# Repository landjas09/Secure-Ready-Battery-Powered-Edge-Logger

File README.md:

# Secure-Ready Battery-Powered Edge Logger

A custom ESP32-C3 hardware/firmware platform, developed across two revisions — from a general-purpose IoT sensor board into a battery-aware, timestamped, secure-ready edge data logger. Designed end-to-end in KiCad, ported to Zephyr RTOS.
This repository contains the full hardware design (schematics, PCB layout, BOM) for both revisions.

---

## Overview

The project began as the **IoT Development Board** (**Rev 1**) — a general-purpose ESP32-C3 sensor/data-logging platform: WiFi/BLE connectivity, environmental and ambient-light sensing, audio capture, local storage, and LiPo charging on a single compact PCB.

**Rev 2, the Secure-Ready Battery-Powered Edge Logger**, evolved that platform with a regulated buck-boost power stage holding 3.3V across the full LiPo discharge range, a battery fuel gauge with Kelvin current sensing, a battery-backed real-time clock for offline timestamping, and a hardware secure element for protected device identity and cryptographic key storage. The name change is deliberate, not cosmetic — it reflects the shift from a general-purpose development board to a system built around a specific mission: unattended, battery-aware, timestamped, secure-ready edge logging.

Both revisions share the same core sensing/storage/connectivity architecture; Rev 2 adds the hardware needed to take the board from *prototype* toward *deployable product*.

---

## Repository Structure

```
├── hardware/
│   ├── rev1/                     # IoT Development Board (original revision)
│   │   ├── README.md             # Full hardware documentation for Rev 1
│   │   └── ...                   # KiCad project, BOM, libraries
│   │
│   └── rev2/                     # Secure-Ready Battery-Powered Edge Logger (current revision)
│       ├── README.md             # Full hardware documentation for Rev 2
│       └── ...                   # KiCad project, BOM, libraries
│

│
└── README.md                     # This file
```

> Each revision is self-contained — its own KiCad project, its own Gerbers/BOM, and its own README with full component-level documentation, block diagrams, and design notes. Start here for the high-level picture, then go to the revision folder for detail.

---

## Hardware Revisions at a Glance

| | Rev 1 — IoT Development Board | Rev 2 — Secure Edge Logger |
|---|---|---|
| MCU | ESP32-C3-WROOM-02-H4 | ESP32-C3-WROOM-02-H4 |
| Power regulation | LM1117-3.3 linear regulator | TPS63802 buck-boost (regulated 3.3V across full LiPo range) |
| Battery charging | MCP73871 (charge + power-path) | MCP73871 (unchanged) |
| Battery state monitoring | Charge-status LEDs only | + BQ27441-G1A fuel gauge, 10mΩ Kelvin current sensing |
| Timekeeping | None (network time only) | + DS3231SN battery-backed RTC |
| Security | None | + NXP EdgeLock SE050E2 secure element |
| Storage | microSD + W25Q32 SPI NOR flash | microSD + W25Q32 SPI NOR flash (unchanged) |
| Sensing | BME280, TEMT6000X01, mic + MAX4466 preamp | Unchanged |
| Connectivity | USB-C, CP2102N USB-UART, OLED I²C header | Unchanged |
| Firmware target | Zephyr RTOS | Zephyr RTOS |

Full rationale for each Rev 2 change — including the buck-boost layout, Kelvin sensing wiring, and shared I²C bus considerations across five devices — is documented in [`hardware/rev2_secure-edge-logger/README.md`](hardware/rev2_secure-edge-logger/README.md).

---

## Design Evolution: The Engineering Behind Rev 1 → Rev 2

Rev 1 answered a narrower question: *can this sensing/connectivity architecture work on a single ESP32-C3 board?* It did — but running it as something closer to an actual field-deployed logger, rather than a bench prototype, surfaced four real limitations that Rev 1's architecture had no answer for. Rev 2 exists specifically to close those four gaps.

**1. The power rail wasn't guaranteed across the battery's actual operating range.**
The LM1117 is a linear regulator — it can only step *down*, and needs a few hundred millivolts of headroom above 3.3V to stay in regulation. A single-cell LiPo spends a meaningful portion of its discharge curve at or below that threshold, well before the cell is actually empty. In practice, that meant the system rail could sag or brown out with real battery capacity still remaining — the board would report "low battery" behavior driven by the regulator's limits, not the battery's. The **TPS63802 buck-boost** converter can step the rail up *or* down as needed, holding a stable 3.3V across the LiPo's full discharge range. The trade-off is real: an inductor-based switching regulator is a more complex layout than a 3-pin LDO (switching-node placement, input/output capacitor proximity), but it removes an artificial ceiling on usable battery capacity.

**2. Battery state was inferred, not measured.**
Rev 1's only battery-state signal was the MCP73871's charge-status LEDs — charging, charged, or power-good. That tells you the *charger's* state, not the battery's: no state-of-charge percentage, no remaining runtime estimate, no visibility into battery health over repeated cycles. For a device meant to log unattended in the field, "the LED is off" isn't useful data. The **BQ27441-G1A fuel gauge**, paired with a 10mΩ Kelvin-sensed shunt for accurate current measurement, gives the firmware real coulomb-counted state-of-charge and capacity data — the difference between guessing how much runtime is left and actually knowing.

**3. Timestamps depended on the network being present, and couldn't survive a real power interruption.**
The ESP32-C3 does have an internal RTC timer, and it runs independently of WiFi — but it has two limitations that make it unsuitable as the sole time source for an offline logger. First, it has no absolute time reference of its own; it only counts elapsed ticks, so it needs to be told the actual date/time at least once, which in Rev 1 meant NTP over WiFi. Second, and more importantly, it has no dedicated backup power domain — it's powered from the same rail as the rest of the chip, so a genuine power interruption (battery disconnected, fully depleted) resets it, and any subsequent logging either loses accurate timestamping or needs a full resync before it can be trusted again. That's a direct conflict with the point of an edge logger, which by definition needs to keep working — and keep accurate time — when disconnected or power-cycled. The **DS3231SN**, with its own dedicated backup supply, keeps ticking through main-power interruptions entirely independently of the ESP32-C3 and of network availability — log integrity no longer depends on the device staying connected or staying powered.

**4. There was no way to prove a device's identity, or protect anything it might need to keep secret.**
Rev 1 had no mechanism for device authentication at all. Any private key or credential would have had to live in the ESP32-C3's own flash — readable by anyone who can extract the chip's contents, meaning a physically compromised device could be cloned or impersonated with no way to detect it. The **SE050E2 secure element** generates and stores keys internally and performs signing/crypto operations without ever exposing key material to the application processor. This is explicitly a *hardware readiness* change, not a finished feature — the chip makes protected device identity possible; actual authentication behavior still has to be implemented and provisioned at the firmware level.

Taken together, Rev 1 — the **IoT Development Board** — validated *that the concept works*. Rev 2 — the **Secure-Ready Battery-Powered Edge Logger** — is the set of changes needed to start asking whether it could actually be *trusted and deployed*: accurate power delivery, real battery visibility, time integrity without a network, and a hardware root of trust. The rename reflects that shift, from a general platform to a system built for a specific job.

---

## Firmware

Both revisions target a common **Zephyr RTOS** board port (`iot_sensor_node_esp32c3`), built from scratch rather than as an overlay on an existing Espressif reference board — the SoC layer is inherited from Zephyr's existing ESP32-C3 support, with Devicetree, pinctrl, and Kconfig scoped to this board's actual hardware.

See [`zephyr/README.md`](https://github.com/landjas09/Zephyr-RTOS-Port/blob/db37eb44f9d1a81693981f7a8ff599a05c521f56/README.md) for the full board architecture, peripheral integration (I²C, SPI, ADC, UART, GPIO), debugging/OpenOCD setup, and the specific integration issues encountered and resolved during the port.

---

## Design Tools

- **Schematic capture & PCB layout:** KiCad 10
- **Electrical/design verification:** KiCad ERC & DRC
- **Firmware / board support:** Zephyr RTOS
- **Secure-element middleware:** NXP Plug & Trust (SE050E2)
- **Hardware configuration:** Silicon Labs Simplicity Studio / Xpress Configurator

---

## Where to Go Next

- **New to the project?** Start with [`hardware/rev1_iot-development-board/README.md`](hardware/rev1_iot-development-board/README.md) for the original, simpler architecture.
- **Interested in the current hardware?** Go to [`hardware/rev2_secure-edge-logger/README.md`](hardware/rev2_secure-edge-logger/README.md) for the full secure edge-logger design.
- **Interested in the firmware/RTOS side?** Go to [`zephyr/README.md`](https://github.com/landjas09/Zephyr-RTOS-Port/blob/db37eb44f9d1a81693981f7a8ff599a05c521f56/README.md) for the board port documentation.

---

## Acknowledgments

Board design informed by manufacturer reference designs and application notes from Espressif, Microchip, Texas Instruments, NXP, Analog Devices/Maxim, Silicon Labs, Bosch Sensortec, Winbond, and the Zephyr Project.

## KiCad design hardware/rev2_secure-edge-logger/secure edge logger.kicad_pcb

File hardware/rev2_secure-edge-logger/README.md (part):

# Secure-Ready Battery-Powered Edge Logger

**ESP32-C3 · KiCad 10 · Zephyr RTOS · Battery monitoring · Offline timekeeping · Secure element**

A custom embedded platform for collecting environmental, light, and acoustic signals, storing data locally, and developing battery-aware logging applications. The hardware combines an ESP32-C3 with a buck-boost power supply, a fuel gauge, a battery-backed RTC, and a dedicated secure element.

*CAD rendering of the revised design. Hardware fabrication and bench validation are pending.*

| Project area | Current state |
|---|---|
| Hardware | Rev 2 schematic and PCB design in KiCad 10 |
| Firmware | Custom Zephyr board port; build validation reported in the firmware repository |
| Physical validation | Pending PCB fabrication and bring-up |
| Security | SE050E2 hardware and middleware integration; application provisioning remains to be completed |
| Manufacturing | NextPCB is the intended manufacturer; procurement and release checks remain open |

## Contents

- [Design evolution](#design-evolution)
- [Rev 2 hardware](#rev-2-hardware)
- [Power architecture](#power-architecture)
- [Interfaces and pin mapping](#interfaces-and-pin-mapping)
- [Programming and debugging](#programming-and-debugging)
- [Firmware integration](#firmware-integration)
- [Manufacturing and validation](#manufacturing-and-validation)
- [Repository and design files](#repository-and-design-files)
- [Technical references](#technical-references)

## Design evolution

The project began as the **IoT Development Board**, a general-purpose ESP32-C3 design combining sensing, wireless connectivity, local storage, USB-to-UART programming, and single-cell battery charging.

**Rev 2** develops that architecture around unattended data logging. Its main additions address supply regulation as the battery discharges, visibility into battery state, timekeeping without a network connection, and protected cryptographic credentials.

| Function | Rev 1 — IoT Development Board | Rev 2 — Secure Edge Logger |
|---|---|---|
| Controller | ESP32-C3-WROOM-02-H4 | ESP32-C3-WROOM-02-H4 |
| System regulation | LM1117-3.3 linear regulator | TPS63802 buck-boost converter |
| Charging / load sharing | MCP73871 | MCP73871 |
| Battery monitoring | Charger status outputs | BQ27441-G1A and 10 mΩ four-terminal shunt |
| Absolute time | Requires a software time source | DS3231SN with separate backup-cell connection |
| Security hardware | ESP32-C3 platform capabilities | Adds NXP EdgeLock SE050E2 |
| Sensors | BME280, TEMT6000, electret microphone and MAX4466 | Same sensing architecture |
| Local storage | External SPI NOR and SD-card socket | Same architecture, with revised bus pull-ups |
| Programming interface | USB-to-UART architecture | CP2102N-A02-GQFN24 with dedicated DTR/RTS outputs |

A linear regulator requires input headroom above its output. A 1S LiPo supply eventually falls below the voltage needed to maintain a regulated 3.3 V rail through an LM1117. The buck-boost stage can both raise and lower its input voltage, extending the usable operating range. Final operation still depends on the pack cutoff, load, conversion losses, and thermal performance.

## Rev 2 hardware

| Subsystem | Reference | Selected device | Interface / role |
|---|---|---|---|
| MCU and radio | U203 | ESP32-C3-WROOM-02-H4 | RISC-V processor, 2.4 GHz Wi-Fi, Bluetooth LE, 4 MiB module flash |
| USB-to-UART | U200 | CP2102N-A02-GQFN24 | UART0 console and programming; DTR/RTS boot control |
| USB data protection | U201 | USBLC6-2SC6 | ESD protection on USB D+/D− |
| Charger / power path | U100 | MCP73871-2CAI/ML | 4.2 V single-cell charging and system load sharing |
| System regulator | IC100 | TPS63802DLAR | Nominal 3.3 V buck-boost conversion |
| Battery fuel gauge | IC101 | BQ27441DRZT-G1A | I²C battery-state estimation |
| Current sensing | R105 | WSK2512R0100FEA | 10 mΩ, four-terminal Kelvin shunt |
| Environmental sensing | U300 | BME280 | Temperature, humidity, and pressure over I²C |
| Ambient light | Q300 | TEMT6000X01 | Analog input to ADC1 |
| Acoustic input | MK300 / U303 | CMC-5042PF-AC / MAX4466EXK+T | Electret microphone and analog preamplifier |
| Real-time clock | U301 | DS3231SN# | I²C calendar/time, alarm or square-wave output |
| Secure element | U302 | SE050E2HQ1/Z01Z3Z | I²C transport for protected keys and cryptographic operations |
| External NOR | U202 | W25Q32JVSSIQ | 32 Mbit / 4 MiB SPI storage, separate from module flash |
| Removable storage | J200 | GSD090012SEU | **Full-size SD** socket, connected for SPI operation |

The microphone path exposes an analog waveform to the MCU. Sampling rate, filtering, calibration, and any acoustic metrics are application responsibilities. The light input likewise requires calibration before reporting an absolute illuminance value.

### PCB construction

The current CAD specifies a **four-layer, 1.60 mm PCB** with an approximate **82.0 × 54.2 mm** outline envelope. The outline includes an antenna clearance cutout; the CAD outline and connector drawings define the enclosure fit.

| Copper layer | Contents in the current design |
|---|---|
| F.Cu | Components, signal routing, and local power/ground pours |
| In1.Cu | Ground zone |
| In2.Cu | Power distribution zones |
| B.Cu | Additional signal routing |

The fabrication stackup and USB differential geometry must be agreed with NextPCB. The stackup stored in CAD alone does not establish the manufactured impedance.

## Power architecture

```mermaid
flowchart TD
    USB["USB-C: 5 V input"] --> FUSE["F100: resettable fuse"]
    FUSE --> MCP["MCP73871: charger and power path"]
    PACK["Protected 1S LiPo pack"] <--> SHUNT["R105: 10 mΩ current shunt"]
    SHUNT <--> MCP
    SHUNT -. "Kelvin sense" .-> GAUGE["BQ27441-G1A"]
    MCP --> SYS["MCP-OUT system supply"]
    SYS --> BUCK["TPS63802 buck-boost"]
    BUCK --> RAIL["3.3 V system rail"]
```

### Charging and system supply

- **Input:** 5 V USB power through J100. Separate 5.1 kΩ resistors terminate CC1 and CC2. The design has no USB Power Delivery controller.
- **Charge target:** the selected MCP73871 variant charges a 1S Li-ion/LiPo pack to 4.2 V. R114 = 2 kΩ requests approximately **500 mA** nominal charge current, subject to available input current and thermal regulation.
- **Input limit:** the current wiring selects the MCP73871 USB mode with a nominal **500 mA total input limit** (`SEL` low, `PROG2` high). The system and charger share that budget. A higher-rated USB adapter does not change these hardware settings.
- **Temperature sensing:** J102 connects an external battery thermistor. The sensor and harness must be selected for the charger and thermally coupled to the pack.
- **Pack protection:** use a qualified protected battery pack with suitable discharge, charge, and temperature ratings. Pack protection provides the required cell cutoff behavior; the charger manages charging and load sharing.

### 3.3 V regulation and battery measurement

The TPS63802 uses a 470 nH inductor and a 511 kΩ / 91 kΩ feedback divider for approximately 3.3 V. `EN` follows the system supply and `MODE` is tied low for power-save operation. The converter's rated current is a component specification; the board's continuous and peak current capability must be established for the complete power path.

The BQ27441 measures battery current across R105 using separate sense connections. Firmware must configure the gauge for the actual pack capacity, charge-termination behavior, and operating limits. Battery runtime, idle consumption, load-step margin, and charging temperature rise remain measurements to establish on the assembled board.

### RTC backup supply

BT300 is a **Keystone 2998 / 2998TR holder**, supplied separately from its cell. Its footprint accepts a 6.8 mm cell; it is incompatible with a CR2032.

The previously considered MS621FE is a rechargeable 3 V cell, but the current PCB provides **no RTC-cell charging circuit**. A final cell and charging/replacement plan must be qualified. Keep the backup supply within the DS3231's specified range, including its 2.3 V minimum. This backup connection supplies the RTC during loss of main power; it does not run the MCU or preserve an unfinished storage write.

## Interfaces and pin mapping

The following assignments come from the revised Rev 2 PCB connections.

### MCU signals

| ESP32-C3 signal | Function | Connected hardware |
|---|---|---|
| GPIO0 / ADC1_CH0 | Microphone input | MAX4466 output |
| GPIO1 / ADC1_CH1 | Light input | TEMT6000 analog node |
| GPIO2 | SPI MISO | SD and external NOR return data |
| GPIO3 | I²C SCL | Shared peripheral bus |
| GPIO4 | I²C SDA | Shared peripheral bus |
| **GPIO5** | **RTC INT/SQW** | DS3231 open-drain output |
| GPIO6 | SPI SCLK | SD and external NOR clock |
| GPIO7 | SPI MOSI | SD CMD / NOR DI |
| **GPIO8** | **SD chip select** | SD DAT3 / CS |
| GPIO9 | BOOT | S400 and automatic boot circuit |
| GPIO10 | External NOR chip select | W25Q32 CS# |
| GPIO18 | Native USB D− / GPIO | BREAKOUT400 pin 2 |
| GPIO19 | Native USB D+ / GPIO | BREAKOUT400 pin 3 |
| GPIO20 / U0RXD | UART receive | CP2102N TXD |
| GPIO21 / U0TXD | UART transmit | CP2102N RXD |
| EN | Hardware enable / reset | S401 and automatic reset circuit |

GPIO2, GPIO8, and GPIO9 are strapping pins. Their levels during reset must remain compatible with boot requirements. Moving the RTC interrupt to GPIO5 prevents an asserted RTC alarm from pulling GPIO8 low during download-mode entry. SD CS has a 10 kΩ pull-up; BOOT uses the ESP32-C3's internal weak pull-up in the current circuit.

### I²C bus

SDA and SCL each have a **4.7 kΩ pull-up to 3.3 V** through R300/R301. The firmware baseline uses 100 kHz. Addresses below use the **7-bit convention**.

| Device | Address | Configuration |
|---|---:|---|
| BME280 | `0x76` | SDO grounded; CSB tied high for I²C |
| BQ27441-G1A | `0x55` | Fixed device address |
| DS3231SN | `0x68` | Fixed device address |
| SE050E2 | `0x48` default | Use the NXP protocol/middleware and confirm provisioned configuration |
| External OLED | Module-dependent | Select the exact controller, address, and application overlay |

The RTC `INT/SQW` connection has its own **4.7 kΩ pull-up** through R303. Firmware selects alarm or square-wave operation and clears the relevant alarm flags when using interrupts. An OLED module's pull-ups combine with the board's pull-ups; verify their voltage and effective resistance.

### Shared SPI storage

SD and NOR share SCLK, MOSI, and MISO with separate active-low chip selects. R205–R208 are 50 Ω series damping resistors; these serve a different purpose from pull-ups.

| Network | Implementation |
|---|---|
| SD DAT3 / CS | 10 kΩ pull-up, R209 |
| SD CMD / MOSI | 10 kΩ pull-up, R210 |
| SD DAT0 / MISO | 10 kΩ pull-up, R211 |
| SD DAT1 and DAT2 | 10 kΩ pull-ups, R212/R213; unused for SPI transfers |
| External NOR CS# | 10 kΩ pull-up, R214 |

During initialization, establish both chip selects high, observe each device's startup timing, and initialize the SD card using its SPI-mode sequence. Use a shared bus lock for transfers. Validate the selected card, clock rate, NOR access, and MISO release with both devices fitted. The socket's card-detect and write-protect contacts are unconnected.

TP1–TP5 provide access to MISO, MOSI, SD CS, NOR CS, and SCLK respectively.

### External connectors

Pin numbers refer to the PCB footprint numbering. Check the physical pin-1 marker and mating cable drawing before connecting a module or pack.

| Connector | Purpose | Pin assignment |
|---|---|---|
| J100 | USB-C | 5 V power and USB data to the CP2102N |
| J101 | Main battery, JST PH 2.00 mm | **1 = GND, 2 = battery positive** |
| J102 | External thermistor, JST ZH 1.50 mm | **1 = THERM, 2 = GND** |
| OLED400 | I²C display header, 2.54 mm | **1 = 3.3 V, 2 = SCL, 3 = SDA, 4 = GND** |
| BREAKOUT400 | Native USB / GPIO header, 2.54 mm | **1 = 3.3 V, 2 = GPIO18, 3 = GPIO19, 4 = GND** |

The OLED header order must be matched with a correctly wired cable. The exact OLED module, SD card, main pack, thermistor harness, and RTC cell are external selections that require final qualification. GPIO8 is occupied by SD CS and is unavailable as a spare expansion signal.

## Programming and debugging

### USB-to-UART and automatic boot

J100 routes USB data through U201 to the **CP2102N-A02-GQFN24**. The bridge uses the board's 3.3 V supply, VBUS sensing, and a 1 kΩ reset pull-up. UART connections cross correctly: bridge TXD to MCU RXD, and bridge RXD to MCU TXD.

The QFN24 package exposes dedicated **DTR# on pin 23** and **RTS# on pin 19**. Q400/Q401 form the two-transistor automatic boot/reset circuit, controlling EN and GPIO9. The EN network uses R402 = 10 kΩ and C401 = 1 µF. C400 on BOOT is marked **DNP**. CTS is unused.

The TX/RX indicator pins require the intended alternate-function configuration in Silicon Labs' configuration tools. Confirm automatic bootloader entry and the CP2102N's USB behavior during bring-up.

### Manual bootloader entry

1. Connect USB and identify the CP2102N serial port.
2. Hold **BOOT** (S400).
3. Press and release **EN** (S401) while continuing to hold BOOT.
4. Release BOOT after the reset sequence, then start the UART upload.
5. Reset with EN after flashing if required by the flashing tool.

### Native USB/JTAG

Native ESP32-C3 USB Serial/JTAG signals are exposed on GPIO18/GPIO19 through BREAKOUT400. J100 is connected to the CP2102N, so native debugging requires a separately qualified connection to the breakout. Preserve signal polarity, routing, protection, and power-domain compatibility when designing that connection.

## Firmware integration

Firmware lives in the separate [Zephyr RTOS Port repository](https://github.com/landjas09/Zephyr-RTOS-Port). The custom target is `iot_sensor_node_esp32c3`; the port is documented against **Zephyr 4.2.0-rc1** and reuses Zephyr's ESP32-C3 SoC support.

The port describes UART, I²C, SPI storage, ADC inputs, BOOT, the RTC, and the fuel gauge through Devicetree and pinctrl. SE050 transport is exposed to **NXP Plug & Trust** through the `se05x-i2c` bus alias. A selected OLED belongs in an application overlay.

The [firmware source snapshot reviewed for this README](https://github.com/landjas09/Zephyr-RTOS-Port/blob/58783257153c90eb4e6a9b5f736847d94d9d9c50/iot_sensor_node_esp32c3.dts) already maps RTC interrupt to GPIO5 and SD CS to GPIO8. Older prose in that repository still shows the previous assignments.

### Configuration to reconcile before hardware testing

| Item | Required alignment |
|---|---|
| External NOR capacity | W25Q32 is **32 Mbit / 4 MiB**. In the reviewed source, `size = <0x400000>;` describes 4 Mbit because the Zephyr `jedec,spi-nor` binding uses **bits**. Set `size = <0x2000000>;` for this device and rebuild. |
| Fuel-gauge configuration | The reviewed source contains a 2000 mAh capacity assumption. Set capacity, taper current, and termination voltage for the qualified pack and charging configuration. |
| Storage clocks | Validate the configured 25 MHz SD ceiling and NOR speed on the assembled board; start conservatively during bring-up. |
| RTC | Initialize valid time, check oscillator-stop status, and implement alarm-flag handling. |
| Security | Define key provisioning, access policy, and the application's signing/authentication workflow. |
| Low-power behavior | Measure the complete board, including bridge, LEDs, sensors, gauge, and storage; MCU sleep current alone is insufficient to predict runtime. |

The firmware repository reports successful build integration. Runtime operation on this PCB remains to be validated. Security features such as signed records, authenticated network sessions, flash encryption, and secure boot each require an explicit implementation and validation plan.

## Manufacturing and validation

### Assembly data

The reviewed Rev 2 CAD contains **109 references**: **103 fitted components**, **one DNP capacitor (C400)**, and **five bare copper test points**. The fitted population includes **42 resistors** and **29 capacitors**.

Generate fabrication and assembly outputs from the same saved revision. The placement file must contain the 103 fitted references and exclude C400 and TP1–TP5. Include the specified through-hole parts in the assembly quotation and agree on their soldering process.

### Release items

The prepared BOM remains a quotation/review document until these items are closed:

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
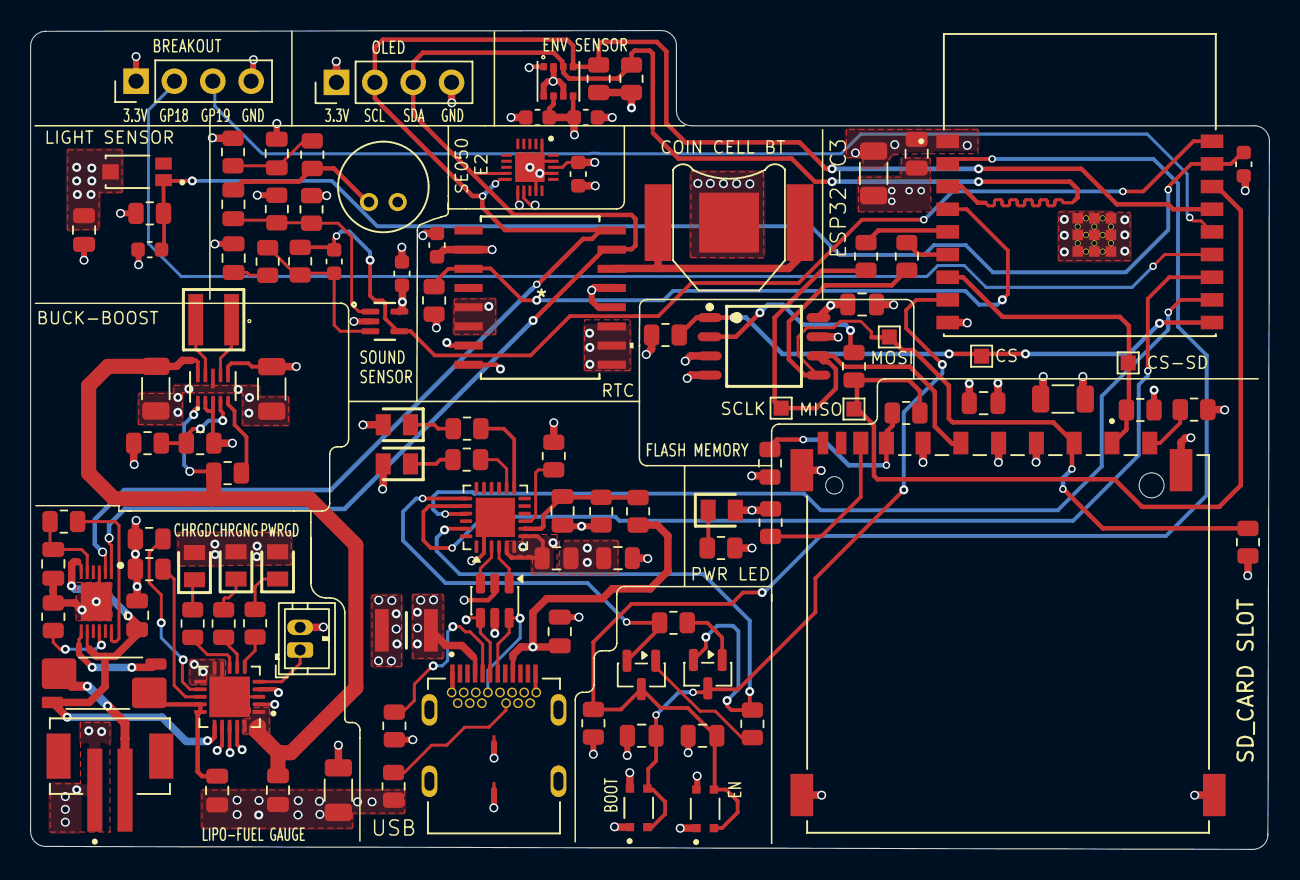
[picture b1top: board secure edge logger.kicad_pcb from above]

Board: 4 copper layers, 82.0 x 54.2 mm, 109 parts (0 on the bottom side), 70 nets.

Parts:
BREAKOUT400: Conn_01x04_Pin; PinHeader_1x04_P2.54mm_Vertical
BT300: Keystone 2998; BatteryHolder_Keystone_2998_1x6.8mm
C100, C201, C202, C203, C204, C207, C305, C309: 0.1u; C_0805_2012Metric
C101, C103, C205, C206: 10u; C_1206_3216Metric
C102, C107, C200: 4.7u; C_0805_2012Metric
C104: 22u; C_1206_3216Metric
C105: 0.47u; C_0805_2012Metric
C106, C307, C401: 1u; C_0805_2012Metric
C300, C310, C311: 100n; C_0603_1608Metric
C301, C302: 10n; C_0603_1608Metric
C303, C304: 100nf; C_0603_1608Metric
C306: 0.01u; C_0805_2012Metric
C308: 100p; C_0603_1608Metric
C400: DNP; C_0805_2012Metric
D100: LTST-C170KRKT; LEDC2012X120N
D101: LTST-C170TBKT; LEDC2012X120N
D102: LTST-C170GKT; LEDC2012X120N
F100: 0ZCH0110AF2E; FUSC3226X100N
IC100: TPS63802DLAR
IC101: BQ27441DRZT-G1A; SON40P400X250X100-13N-D
J100: SS-52400-003; BELFUSE_SS-52400-003
J101: B2B-PH-SM4-TB; JST_B2B-PH-SM4-TB
J102: Conn_01x02; JST_ZH_B2B-ZR_1x02_P1.50mm_Vertical
J200: GSD090012SEU; AMPHENOL_GSD090012SEU
L100: XFL4015-471MEC; XFL4012
MK300: CMC-5042PF-AC; CUI_CMC-5042PF-AC
OLED400: Conn_01x04_Pin; PinHeader_1x04_P2.54mm_Vertical
PWR100: LTST-C170KRKT; LEDC2012X120N
Q300: TEMT6000X01; TRANS_TEMT6000X01
Q400, Q401: BC817; SOT-23
R100, R101: 5K1; R_0805_2012Metric
R102, R103, R104, R111, R203, R204: 470; R_0805_2012Metric
R105: 10m; R_Shunt_Vishay_WSK2512_6332Metric_T1.19mm
R107: 20K; R_0805_2012Metric
R108: 511k; R_0805_2012Metric
R109: 91k; R_0805_2012Metric
R110: 100k; R_0805_2012Metric
R112, R113, R210, R211, R212, R213, R214, R307: 10k; R_0805_2012Metric
R114: 2K; R_0805_2012Metric
R200: 1k; R_0805_2012Metric
R201: 22K1; R_0805_2012Metric
R202: 47K5; R_0805_2012Metric
R205, R206, R207, R208: 50; R_0805_2012Metric
R209, R302, R400, R401, R402: 10K; R_0805_2012Metric
R300, R301: 4.7k; R_0805_2012Metric
R303: 4,7k; R_0805_2012Metric
R304, R305: 2k; R_0805_2012Metric
R306, R308: 1M; R_0805_2012Metric
R309: 100K; R_0805_2012Metric
RX200: LTST-C170KRKT; LEDC2012X120N
S400: BOOT; SW_USLPT2819DT2TR
S401: ENABLE; SW_USLPT2819DT2TR
TP1: TestMISO; TestPoint_Pad_1.0x1.0mm
TP2: TestMOSI; TestPoint_Pad_1.0x1.0mm
TP3: TestSD; TestPoint_Pad_1.0x1.0mm
TP4: TestCS; TestPoint_Pad_1.0x1.0mm
TP5: TestCLK; TestPoint_Pad_1.0x1.0mm
TX200: LTST-C170GKT; LEDC2012X120N
U100: MCP73871-2CAI_ML; QFN50P400X400X100-21N
U200: CP2102N-Axx-xQFN24; QFN-24-1EP_4x4mm_P0.5mm_EP2.6x2.6mm
U201: USBLC6-2SC6; SOT-23-6
U202: W25Q32JVSSIQ; SOIC127P790X216-8N
U203: ESP32-C3-WROOM-02-H4; ESP32--C3-WROOM-02-H4
U300: BME280; PSON65P250X250X100-8N
U301: ds3231sn-; 21-0042B_16_MXM
U302: SE050E2HQ1/Z01Z3Z; QFN40P300X300X33-21N-D
U303: MAX4466EXK; SOT65P210X110-5N

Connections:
+3.3V: BREAKOUT400.1, C104.2, C200.1, C201.2, C203.2, C204.1, C205.1, C206.1, C207.1, C300.2, C303.1, C304.1, C309.1, C310.2, C311.2, IC100.6 (VOUT), J200.4 (VDD1), OLED400.1, PWR100.2 (A), Q300.3, R108.1, R200.1, R209.1, R210.2, R211.2, R212.2, R213.2, R214.2, R300.1, R301.1, R303.1, R304.2, R306.2, R402.2, RX200.2 (A), TX200.2 (A), U200.5 (VIO), U200.6 (VDD), U200.7 (VREGIN), U202.3 (~WP(IO2)), U202.7 (~HOLD/~RESET(IO3)), U202.8 (VCC), U203.1 (3V3), U300.2 (CSB), U300.6 (VDDIO), U300.8 (VDD), U301.2 (VCC), U302.11 (ENA), U302.12 (VIN), U302.18 (VCC), U303.5 (VCC)
/+5V-USB: C101.1, D100.2 (A), D101.2 (A), D102.2 (A), F100.2, U100.2 (VPCC), U100.4 (PROG2), U100.17 (CE), U100.18 (IN), U100.19 (IN)
/BAT JST+: C106.1, IC101.6 (BAT), IC101.8 (SRP), R105.2, U100.16 (VBAT_SENSE)
/CHARGED: R104.1, U100.8 (STAT1/~LBO)
/CHARGING: R102.1, U100.6 (~PG)
/CHARGING-POWE-GOOD: R103.1, U100.7 (STAT2)
/ESP32-C3-02/BOOT: C400.1, Q401.3 (C), S400.3, S400.4, U203.8 (IO9)
/ESP32-C3-02/CS: R214.1, TP4.1 (1_1), U202.1 (~CS), U203.10 (IO10)
/ESP32-C3-02/CS-SD: J200.1 (CD/DAT3), R209.2, TP3.1 (1_1), U203.7 (IO8)
/ESP32-C3-02/DAT1: J200.8 (DAT1), R212.1
/ESP32-C3-02/DAT2: J200.9 (DAT2), R213.1
/ESP32-C3-02/DTR: Q401.2 (E), R400.1, U200.23 (~DTR)
/ESP32-C3-02/EN: C401.1, Q400.3 (C), R402.1, S401.3, S401.4, U203.2 (EN)
/ESP32-C3-02/GPIO18: BREAKOUT400.2, U203.13 (IO18)
/ESP32-C3-02/GPIO19: BREAKOUT400.3, U203.14 (IO19)
/ESP32-C3-02/INT/SQW: R303.2, U203.4 (IO5), U301.3 (*INT/SQW)
/ESP32-C3-02/MIC_OUT: C308.2, R309.2, U203.18 (IO0), U303.4 (OUT)
/ESP32-C3-02/MISO-ESP: R207.1, U203.6 (IO7)
/ESP32-C3-02/MISO-GSD: J200.7 (DAT0), R208.1, R211.1
/ESP32-C3-02/MISO-W25: R205.1, U202.2 (DO(IO1))
/ESP32-C3-02/MISO_DO: R205.2, R208.2, TP1.1 (1_1), U203.16 (IO2)
/ESP32-C3-02/MOSI-DI: J200.2 (CMD), R207.2, R210.1, TP2.1 (1_1), U202.5 (DI(IO0))
/ESP32-C3-02/NRST: R200.2, U200.9 (~RST)
/ESP32-C3-02/NRXT: R204.1, U200.13 (~RXT/GPIO.1)
/ESP32-C3-02/NTXT: R203.1, U200.14 (~TXT/GPIO.0)
/ESP32-C3-02/PHOTO-C: C301.1, C302.1, Q300.1, R302.1, U203.17 (IO1)
/ESP32-C3-02/RTS: Q400.2 (E), R401.1, U200.19 (~RTS)
/ESP32-C3-02/RX-TX: U200.20 (RXD), U203.12 (TXD)
/ESP32-C3-02/SCLK: J200.5 (CLK), R206.1, TP5.1 (1_1), U202.6 (CLK)
/ESP32-C3-02/SCLK-ESP: R206.2, U203.5 (IO6)
/ESP32-C3-02/SENSORS/VBAT-DS: BT300.1 (+), U301.14 (VBAT)
/ESP32-C3-02/TX-RX: U200.21 (TXD), U203.11 (RXD)
/ESP32-C3-02/USB_D+: U200.3 (D+), U201.3 (I/O2)
/ESP32-C3-02/USB_D-: U200.4 (D-), U201.1 (I/O1)
/ESP32-C3-02/VBUS-CP: C202.2, R201.1, R202.2, U200.8 (VBUS)
/MCP-OUT: C102.2, C103.2, IC100.1 (EN), IC100.10 (VIN), R110.2, U100.1 (OUT), U100.20 (OUT)
/SCL: IC101.2 (SCL), OLED400.2, R301.2, U203.15 (IO3), U300.4 (SCK), U301.16 (SCL), U302.10 (L2C_SCL)
/SDA: IC101.1 (SDA), OLED400.3, R300.2, U203.3 (IO4), U300.3 (SDI), U301.15 (SDA), U302.9 (L2C_SDA)
/THERM: J102.1, U100.5 (THERM)
/USB-DN: J100.A7 (DN1), J100.B7 (DN2), U201.6 (I/O1)
/USB-DP: J100.A6 (DP1), J100.B6 (DP2), U201.4 (I/O2)
/VBAT: J101.2, R105.1
/VBAT_SYS: IC101.7 (SRN), R105.3
/VBUS: C100.2, F100.1, J100.A4 (VBUSA1), J100.A9 (VBUSA2), J100.B4 (VBUSB1), J100.B9 (VBUSB2), R201.2, U201.5 (VBUS)
/VDD_BQ27441: C105.1, IC101.5 (VDD), R112.2
GND: BREAKOUT400.4, BT300.2 (-), C100.1, C101.2, C102.1, C103.1, C104.1, C105.2, C106.2, C107.2, C200.2, C201.1, C202.1, C203.1, C204.2, C205.2, C206.2, C207.2, C300.1, C301.2, C302.2, C303.2, C304.2, C305.1, C307.1, C309.2, C310.1, C311.1, C400.2, C401.2, IC100.2 (MODE), IC100.3 (AGND), IC100.8 (GND), IC101.3 (VSS), IC101.13 (THERMAL_PAD), J100.A1 (GNDA1), J100.A12 (GNDA2), J100.B1 (GNDB1), J100.B12 (GNDB2), J100.G1 (GND/SHIELD), J100.G2 (GND/SHIELD), J100.G3 (GND/SHIELD), J100.G4 (GND/SHIELD), J100.S1 (GND/SHIELD), J100.S2 (GND/SHIELD), J100.S3 (GND/SHIELD), J100.S4 (GND/SHIELD), J101.1, J102.2, J200.3 (VSS1), J200.6 (VSS2), J200.G1 (SHIELD_GND), J200.G2 (SHIELD_GND), J200.G3 (SHIELD_GND), J200.G4 (SHIELD_GND), MK300.GND, OLED400.4, R100.2, R101.2, R107.2, R109.2, R111.1, R113.2, R114.2, R202.1, R302.2, R308.1, S400.1, S400.2, S401.1, S401.2, U100.3 (SEL), U100.9 (~TE), U100.10 (VSS), U100.11 (VSS), U100.21 (VSS), U200.2 (GND), U200.25 (GND), U201.2 (GND), U202.4 (GND), U203.9 (GND), U203.19 (GND), U203.20 (GND), U203.21 (GND), U203.22 (GND), U203.23 (GND), U203.24 (GND), U203.25 (GND), U203.26 (GND), U203.27 (GND), U203.28 (GND), U203.29 (GND), U203.30 (GND), U203.31 (GND), U203.32 (GND), U203.33 (GND), U203.34 (GND), U203.35 (GND), U203.36 (GND), U203.37 (GND), U203.38 (GND), U203.39 (GND), U300.1 (GND), U300.5 (SDO), U300.7 (GND), U301.5 (NC), U301.6 (NC), U301.7 (NC), U301.8 (NC), U301.9 (NC), U301.10 (NC), U301.11 (NC), U301.12 (NC), U301.13 (GND), U302.1 (ISO_14443_LB), U302.14 (ISO_7816_RST_N), U302.17 (ISO_14443_LA), U302.19 (VSS), U302.21 (EPAD), U303.2 (GND)
unnamed: C305.2, R304.1, R305.2
unnamed: C306.2, MK300.OUT, R305.1
unnamed: C307.2, R307.1
unnamed: D100.1 (K), R102.2
unnamed: D101.1 (K), R103.2
unnamed: D102.1 (K), R104.2
unnamed: IC100.4 (FB), R108.2, R109.1
unnamed: IC100.9 (L1), L100.2
unnamed: IC100.7 (L2), L100.1
unnamed: IC100.5 (PG), R110.1
unnamed: IC101.10 (BIN), R113.1
unnamed: IC101.12 (GPOUT), R112.1
unnamed: J100.A5 (CC1), R100.1
unnamed: J100.B5 (CC2), R101.1
unnamed: PWR100.1 (K), R111.2
unnamed: Q400.1 (B), R400.2
unnamed: Q401.1 (B), R401.2
unnamed: R204.2, RX200.1 (K)
unnamed: R203.2, TX200.1 (K)
unnamed: R114.1, U100.13 (PROG1)
unnamed: R107.1, U100.12 (PROG3)
unnamed: C107.1, R105.4, U100.14 (VBAT), U100.15 (VBAT)
unnamed: C306.1, R306.1, R308.2, U303.1 (IN+)
unnamed: C308.1, R307.2, R309.1, U303.3 (IN-)

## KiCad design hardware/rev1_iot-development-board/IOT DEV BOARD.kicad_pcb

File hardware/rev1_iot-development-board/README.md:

# Custom IoT Development Board — ESP32-C3

A custom-designed IoT development board built around the **ESP32-C3-WROOM-02**, featuring integrated LiPo battery charging, environmental sensing, ambient light sensing, audio capture, on-board storage (flash + SD card), and a USB-C interface with full USB-to-UART programming support. Designed end-to-end in **KiCad 10**, from schematic capture through PCB layout and routing.

---

## Overview

This board was designed as a general-purpose sensor/data-logging platform for IoT applications — combining wireless connectivity (WiFi/BLE via the ESP32-C3), multiple onboard sensors, local storage, and rechargeable battery power into a single compact PCB.

## Aplications
- IoT edge devices for environmental monitoring.
- Battery-powered data logging systems.
- Prototyping platform for ESP32-based projects.

**Key design goals:**
- Fully USB-C powered and rechargeable (no external charger required)
- Onboard environmental, light, and audio sensing
- Local data logging via SD card, with dedicated flash for firmware/configuration
- Standard USB-to-UART programming/debugging, no external programmer needed
- Expandable via an I²C OLED connector and a breakout header for spare GPIOs

---

## Block Diagram

```mermaid
flowchart LR
    USB[USB-C Connector<br/>SS-52400-002] --> ESD[ESD Protection<br/>USBLC6-2SC6]
    USB --> CHG[LiPo Charger<br/>MCP73871-2CAI_ML]
    ESD --> UART[USB-UART Bridge<br/>CP2102N-Axx-xQFN20]
    UART <--> MCU[ESP32-C3-WROOM-02-H4]

    CHG --> BAT[JST LiPo Battery Connector]
    CHG --> REG[3.3V Regulator<br/>LM1117MPX-3.3]
    REG --> MCU
    CHG --> LED1[Charge Status LEDs]

    MCU <-->|I2C| BME[BME280<br/>Humidity + Pressure]
    MCU <-->|ADC| LDR[TEMT6000X01<br/>Ambient Light]
    MCU <-->|ADC| MIC[CMC-5042PF-AC + MAX4466EXK<br/>Mic + Amplifier]
    MCU <-->|SPI| FLASH[W25Q32JVSSIQ<br/>External Flash]
    MCU <-->|SPI| SD[GSD090012SEU<br/>microSD Card]
    MCU <-->|I2C| OLED[OLED Display Header]

    MCU --> BOOT[BOOT / EN Buttons]
    MCU --> GPIO[Spare GPIO Breakout]
```

---

## Hardware Overview

### Power Subsystem
| Component | Part Number | Function |
|---|---|---|
| USB-C Connector | SS-52400-002 | Main power/data input |
| ESD Protection | USBLC6-2SC6 | Protects USB D+/D- from ESD transients |
| LiPo Charger IC | MCP73871-2CAI_ML | Single-cell Li-Ion/LiPo charge management with power-path support |
| Voltage Regulator | LM1117MPX-3.3_NOPB | Regulates system rail to 3.3V |
| Battery Connector | JST 2-pin | Single-cell LiPo battery input |
| Status Indicators | LED x3 | Charging / Charged / Power-Good status |

The MCP73871's integrated power-path management allows the board to run directly from USB power while simultaneously charging the battery, and seamlessly switches to battery power when USB is disconnected — with no interruption to the system rail.

### Core & Connectivity
| Component | Part Number | Function |
|---|---|---|
| MCU | ESP32-C3-WROOM-02-H4 | RISC-V, WiFi + BLE, main system controller |
| USB-UART Bridge | CP2102N-Axx-xQFN20 | USB-to-serial for programming/debugging |
| Flash Memory | W25Q32JVSSIQ | 32Mbit external SPI flash (firmware/config storage) |
| SD Card Socket | GSD090012SEU | microSD card slot (bulk data storage: logs, audio, images) |

Programming and debugging are handled over native USB via the CP2102N, with automatic bootloader entry through a DTR/RTS-driven transistor reset circuit, plus manual BOOT and EN pushbuttons as a hardware fallback.

### Sensors
| Component | Part Number | Interface | Function |
|---|---|---|---|
| Environmental Sensor | BME280 | I²C | Humidity, barometric pressure, temperature |
| Ambient Light Sensor | TEMT6000X01 | Analog (ADC) | Ambient light intensity |
| Microphone Capsule | CMC-5042PF-AC | Analog | Electret condenser microphone |
| Mic Preamplifier | MAX4466EXK+T | Analog (ADC) | Adjustable-gain (25x–125x) microphone amplifier |

### User Interface / Expansion
- **BOOT** and **EN** pushbuttons for manual firmware flashing / reset
- **OLED display header** (I²C, 4-pin) for an external SSD1306-style display
- **Breakout header** exposing spare GPIOs (GPIO8, GPIO18, GPIO19) plus 3.3V/GND for future expansion

---

## Shared Bus Architecture

**SPI bus** (SD card + external flash, daisy-chained MOSI/MISO/SCLK, independent CS lines):
```
ESP32 MOSI ──┬──▶ SD Card MOSI ──▶ Flash MOSI
ESP32 MISO ──┼──◀ SD Card MISO ──◀ Flash MISO
ESP32 SCLK ──┴──▶ SD Card SCLK ──▶ Flash SCLK
ESP32 CS1  ─────▶ SD Card CS (dedicated)
ESP32 CS2  ─────▶ Flash CS (dedicated)
```

**I²C bus** (BME280 + OLED header, shared SDA/SCL with pull-ups):
```
ESP32 SDA ──┬──▶ BME280 SDA
            └──▶ OLED SDA
ESP32 SCL ──┬──▶ BME280 SCL
            └──▶ OLED SCL
```

---

## Design Tools

- **Schematic capture & PCB layout:** KiCad 10
- **Simulation/verification:** KiCad ERC & DRC (Electrical Rules Checker / Design Rules Checker)
- **Firmware:** successfully migrated to **Zephyr RTOS**
- **Hardware config tools:** Silicon Labs Simplicity Studio (for one-time CP2102N GPIO/TXT-RXT configuration)

---

## Repository Structure

This is a native **KiCad 10** project — the schematic is split hierarchically across multiple sheets, with sensors and user-interface elements broken out into their own sub-sheet files for readability.

```
├── IOT DEV BOARD.kicad_pro       # Main KiCad project file
├── IOT DEV BOARD.kicad_sch       # Root schematic sheet
├── IOT DEV BOARD.kicad_pcb       # PCB layout
├── ESP32-C3-02.kicad_sch         # Sub-sheet: MCU + core connectivity
├── sensors.kicad_sch             # Sub-sheet: BME280, light sensor, mic/amp
├── userInterface.kicad_sch       # Sub-sheet: BOOT/EN buttons, OLED header, breakout
│
├── ESP32_IOT_BOARD_GERBER/       # Exported Gerber/drill files for fabrication
├── Libraries/                    # Custom footprints and symbols
├── BOM.csv                       # Bill of materials
├── fp-lib-table                  # Footprint library table
├── sym-lib-table                 # Symbol library table
└── output.json                   # Exported netlist/data
```

> Lock files (`*.lck`), `.history/`, and `.git/` are local/version-control housekeeping and not part of the design itself.

---

## Known Issues & Design Notes

- **GPIO5 / ADC2 conflict:** GPIO5 is the ESP32-C3's only ADC2 channel, and ADC2 is unreliable while WiFi is active (and affected by a known silicon errata on some chip revisions). Analog signals (e.g. microphone, light sensor) must use **ADC1 pins (GPIO0–GPIO4)** instead.
- **CP2102N TXT/RXT indicator LEDs:** these pins default to plain GPIO mode from the factory and do **not** blink out of the box — they must be explicitly configured via Silicon Labs' **Xpress Configurator** (Simplicity Studio) to enable the TXT/RXT alternate function.
- **CP2102N QFN20 package** does not expose a physical DTR pin — DTR emulation for the auto-reset circuit is handled via a reconfigured spare GPIO, not a dedicated pin.
- **SD card DAT3/CS line** requires a pull-up resistor to guarantee the card boots into SPI mode rather than native SD mode at power-up.

---

## Planned Additions

- **DS3231SN** real-time clock (I²C) for accurate timestamping of logged sensor data, independent of network time availability.
- **Enclosure design (SolidWorks)** — case built around the board's exported KiCad STEP file, with cutouts for the USB-C port, BOOT/EN buttons, status LEDs, SD card slot, and a light-transmissive window over the ambient light sensor.

---

## Acknowledgments

Board design informed by manufacturer reference designs and application notes from Microchip, Silicon Labs, Espressif, and Winbond.

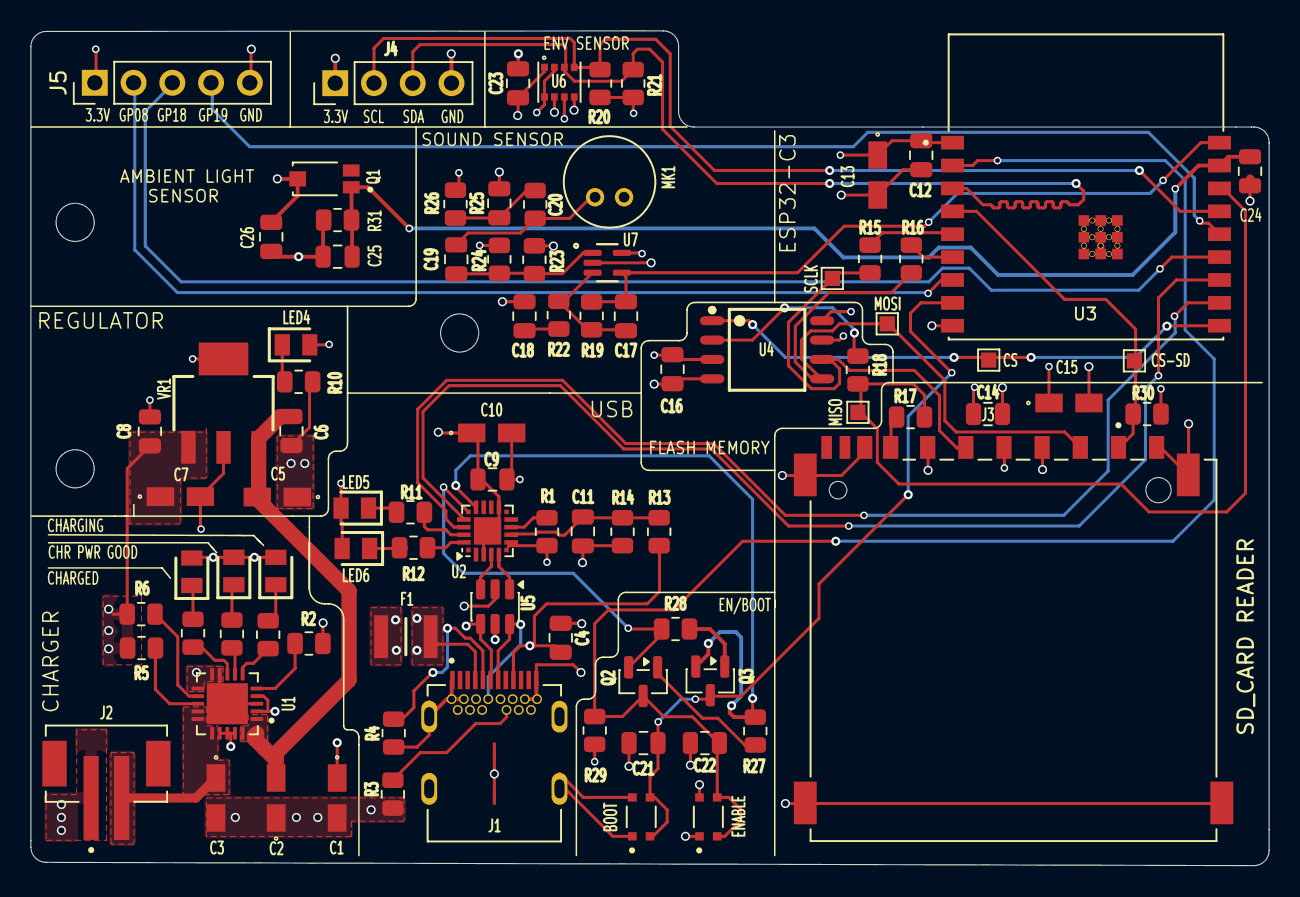
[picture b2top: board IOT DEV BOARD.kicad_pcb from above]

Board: 4 copper layers, 81.2 x 54.7 mm, 91 parts (0 on the bottom side), 57 nets.

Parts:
BOOT: BOOT; SW_USLPT2819DT2TR
C1, C5, C7, C15: 10u; T491A
C2, C3, C10: 4.7u; T491A
C4, C6, C8, C9, C11, C14, C16, C20, C21, C22, C26: 0.1u; C_0805_2012Metric
C12: 0.1U; C_0805_2012Metric
C13: 1Ou; T491A
C17: 100p; C_0805_2012Metric
C18: 1u; C_0805_2012Metric
C19: 0.01u; C_0805_2012Metric
C23: 100n; C_0805_2012Metric
C24, C25: 10n; C_0805_2012Metric
CS: TestCS; TestPoint_Pad_1.0x1.0mm
CS-SD: TestSD; TestPoint_Pad_1.0x1.0mm
ENABLE: ENABLE; SW_USLPT2819DT2TR
F1: 0ZCH0110AF2E; FUSC3226X100N
J1: SS-52400-002; BELFUSE_SS-52400-002
J2: B2B-PH-SM4-TB; JST_B2B-PH-SM4-TB
J3: GSD090012SEU; AMPHENOL_GSD090012SEU
J4: Conn_01x04_Pin; PinHeader_1x04_P2.54mm_Vertical
J5: Conn_01x05_Pin; PinHeader_1x05_P2.54mm_Vertical
LED1, LED4, LED5: LTST-C170KRKT; LEDC2012X120N
LED2, LED6: LTST-C170GKT; LEDC2012X120N
LED3: LTST-C170TBKT; LEDC2012X120N
MH01, MH01#2, MH03: MountingHole_2.5mm
MISO: TestMISO; TestPoint_Pad_1.0x1.0mm
MK1: CMC-5042PF-AC; CUI_CMC-5042PF-AC
MOSI: TestMOSI; TestPoint_Pad_1.0x1.0mm
Q1: TEMT6000X01; TRANS_TEMT6000X01
Q2, Q3: BC817; SOT-23
R1: 1k; R_0805_2012Metric
R2, R27, R28, R29, R30, R31: 10K; R_0805_2012Metric
R3, R4: 5K1; R_0805_2012Metric
R5: 2K; R_0805_2012Metric
R6: 20K; R_0805_2012Metric
R7, R8, R9, R10, R11, R12: 470; R_0805_2012Metric
R13: 22K1; R_0805_2012Metric
R14: 47K5; R_0805_2012Metric
R15, R16, R17, R18: 50; R_0805_2012Metric
R19: 100K; R_0805_2012Metric
R20, R21: R; R_0805_2012Metric
R22: 10k; R_0805_2012Metric
R23, R24: 1M; R_0805_2012Metric
R25, R26: 2k; R_0805_2012Metric
SCLK: TestCLK; TestPoint_Pad_1.0x1.0mm
U1: MCP73871-2CAI_ML; QFN50P400X400X100-21N
U2: CP2102N-Axx-xQFN20; SiliconLabs_QFN-20-1EP_3x3mm_P0.5mm_EP1.8x1.8mm
U3: ESP32-C3-WROOM-02-H4; MODULE_ESP32-C3-WROOM-02-H4
U4: W25Q32JVSSIQ; SOIC127P790X216-8N
U5: USBLC6-2SC6; SOT-23-6
U6: BME280; PSON65P250X250X100-8N
U7: MAX4466EXK; SOT65P210X110-5N
VR1: LM1117MPX-3.3_NOPB; VREG_LM1117MPX-3.3

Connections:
+3.3V: C7.2, C8.2, C9.2, C10.2, C12.1, C13.1, C14.1, C15.1, C16.2, C23.2, C26.1, J3.4 (VDD1), J4.1, J5.1, LED4.2 (A), LED5.2 (A), LED6.2 (A), Q1.3, R1.1, R20.1, R21.1, R24.2, R26.2, R29.2, R30.1, U2.6 (VDD), U2.7 (VREGIN), U3.1 (3V3), U4.3 (~WP(IO2)), U4.7 (~HOLD/~RESET(IO3)), U4.8 (VCC), U6.2 (CSB), U6.6 (VDDIO), U6.8 (VDD), U7.5 (VCC), VR1.2 (VOUT_2), VR1.4 (VOUT_4)
+5V: C2.2, C5.2, C6.2, U1.1 (OUT), U1.20 (OUT), VR1.3 (VIN)
/+5V-USB: C1.1, F1.2, LED1.2 (A), LED2.2 (A), LED3.2 (A), U1.2 (VPCC), U1.4 (PROG2), U1.17 (CE), U1.18 (IN), U1.19 (IN)
/CHARGED: R9.1, U1.8 (STAT1/~LBO)
/CHARGING: R7.1, U1.6 (~PG)
/CHARGING-POWE-GOOD: R8.1, U1.7 (STAT2)
/ESP32-C3-02/BOOT: BOOT.3, BOOT.4, C21.1, Q3.3 (C), U3.8 (IO9)
/ESP32-C3-02/CS: CS.1 (1_1), U3.10 (IO10), U4.1 (~CS)
/ESP32-C3-02/CS-SD: CS-SD.1 (1_1), J3.1 (CD/DAT3), R30.2, U3.4 (IO5)
/ESP32-C3-02/DTS: Q3.2 (E), R27.1, U2.15 (~CTS)
/ESP32-C3-02/EN: C22.1, ENABLE.3, ENABLE.4, Q2.3 (C), R29.1, U3.2 (EN)
/ESP32-C3-02/GPIO08: J5.2, U3.7 (IO8)
/ESP32-C3-02/GPIO18: J5.3, U3.13 (IO18)
/ESP32-C3-02/GPIO19: J5.4, U3.14 (IO19)
/ESP32-C3-02/MIC_OUT: C17.2, R19.2, U3.18 (IO0), U7.4 (OUT)
/ESP32-C3-02/MISO_DO: MISO.1 (1_1), R17.2, R18.2, U3.16 (IO2)
/ESP32-C3-02/MOSI-DI: J3.2 (CMD), MOSI.1 (1_1), R16.2, U4.5 (DI(IO0))
/ESP32-C3-02/PHOTO-C: C24.1, C25.1, Q1.1, R31.1, U3.17 (IO1)
/ESP32-C3-02/RTS: Q2.2 (E), R28.1, U2.16 (~RTS)
/ESP32-C3-02/RX-TX: U2.17 (RXD), U3.12 (TXD)
/ESP32-C3-02/SCL: J4.2, R20.2, U3.15 (IO3), U6.4 (SCK)
/ESP32-C3-02/SCLK: J3.5 (CLK), R15.1, SCLK.1 (1_1), U4.6 (CLK)
/ESP32-C3-02/SDA: J4.3, R21.2, U3.3 (IO4), U6.3 (SDI)
/ESP32-C3-02/TX-RX: U2.18 (TXD), U3.11 (RXD)
/ESP32-C3-02/USB_D+: U2.4 (D+), U5.3 (I/O2)
/ESP32-C3-02/USB_D-: U2.5 (D-), U5.1 (I/O1)
/USB-DN: J1.A7 (DN1), J1.B7 (DN2), U5.6 (I/O1)
/USB-DP: J1.A6 (DP1), J1.B6 (DP2), U5.4 (I/O2)
/VBAT: C3.1, J2.2, U1.14 (VBAT), U1.15 (VBAT), U1.16 (VBAT_SENSE)
/VBUS: C4.2, F1.1, J1.A4 (VBUSA1), J1.A9 (VBUSA2), J1.B4 (VBUSB1), J1.B9 (VBUSB2), R13.2, U5.5 (VBUS)
GND: BOOT.1, BOOT.2, C1.2, C2.1, C3.2, C4.1, C5.1, C6.1, C7.1, C8.1, C9.1, C10.1, C11.1, C12.2, C13.2, C14.2, C15.2, C16.1, C18.1, C20.1, C21.2, C22.2, C23.1, C24.2, C25.2, C26.2, ENABLE.1, ENABLE.2, J1.A1 (GNDA1), J1.A12 (GNDA2), J1.B1 (GNDB1), J1.B12 (GNDB2), J1.G1 (GND/SHIELD), J1.G2 (GND/SHIELD), J1.G3 (GND/SHIELD), J1.G4 (GND/SHIELD), J1.S1 (GND/SHIELD), J1.S2 (GND/SHIELD), J1.S3 (GND/SHIELD), J1.S4 (GND/SHIELD), J2.1, J3.3 (VSS1), J3.6 (VSS2), J3.8 (DAT1), J3.9 (DAT2), J3.G1 (SHIELD_GND), J3.G2 (SHIELD_GND), J3.G3 (SHIELD_GND), J3.G4 (SHIELD_GND), J4.4, J5.5, MK1.GND, R2.2, R3.2, R4.2, R5.2, R6.2, R10.1, R14.1, R23.1, R31.2, U1.3 (SEL), U1.9 (~TE), U1.10 (VSS), U1.11 (VSS), U1.21 (VSS), U2.3 (GND), U2.12 (GND), U2.21 (GND), U3.9 (GND), U3.19 (GND), U3.20 (GND), U3.21 (GND), U3.22 (GND), U3.23 (GND), U3.24 (GND), U3.25 (GND), U3.26 (GND), U3.27 (GND), U3.28 (GND), U3.29 (GND), U3.30 (GND), U3.31 (GND), U3.32 (GND), U3.33 (GND), U3.34 (GND), U3.35 (GND), U3.36 (GND), U3.37 (GND), U3.38 (GND), U3.39 (GND), U4.4 (GND), U5.2 (GND), U6.1 (GND), U6.5 (SDO), U6.7 (GND), U7.2 (GND), VR1.1 (GND)
unnamed: C18.2, R22.1
unnamed: C19.2, MK1.OUT, R25.1
unnamed: C20.2, R25.2, R26.1
unnamed: J1.A5 (CC1), R4.1
unnamed: J1.B5 (CC2), R3.1
unnamed: J3.7 (DAT0), R17.1
unnamed: LED1.1 (K), R7.2
unnamed: LED2.1 (K), R9.2
unnamed: LED3.1 (K), R8.2
unnamed: LED4.1 (K), R10.2
unnamed: LED5.1 (K), R11.2
unnamed: LED6.1 (K), R12.2
unnamed: Q2.1 (B), R27.2
unnamed: Q3.1 (B), R28.2
unnamed: R5.1, U1.13 (PROG1)
unnamed: R6.1, U1.12 (PROG3)
unnamed: R2.1, U1.5 (THERM)
unnamed: C11.2, R13.1, R14.2, U2.8 (VBUS)
unnamed: R1.2, U2.9 (~RST)
unnamed: R11.1, U2.19 (~RXT/GPIO.3)
unnamed: R12.1, U2.20 (~TXT/GPIO.2)
unnamed: R15.2, U3.5 (IO6)
unnamed: R16.1, U3.6 (IO7)
unnamed: R18.1, U4.2 (DO(IO1))
unnamed: C19.1, R23.2, R24.1, U7.1 (IN+)
unnamed: C17.1, R19.1, R22.2, U7.3 (IN-)

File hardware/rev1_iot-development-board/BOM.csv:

"Reference","Qty","Value","Footprint","MANUFACTURER","Description"
"VR1","1","LM1117MPX-3.3_NOPB","ESP32Footprints:VREG_LM1117MPX-3.3","Texas Instruments","800-mA 15-V linear voltage regulator"
"U7","1","MAX4466EXK","ESP32Footprints:SOT65P210X110-5N","","Amplifier IC 1-Channel (Mono) Class AB SC-70-5"
"U6","1","BME280","ESP32Footprints:PSON65P250X250X100-8N","","Board Mount Humidity Sensors MEMS humidity, pressure and temperature sensor"
"U5","1","USBLC6-2SC6","Package_TO_SOT_SMD:SOT-23-6","","Very low capacitance ESD protection diode, 2 data-line, SOT-23-6"
"U4","1","W25Q32JVSSIQ","ESP32Footprints:SOIC127P790X216-8N","","FLASH - NOR Memory IC 32Mb (4M x 8) SPI - Quad I/O 133 MHz 8-SOIC"
"U3","1","ESP32-C3-WROOM-02-H4","ESP32Footprints:MODULE_ESP32-C3-WROOM-02-H4","","WiFi Modules (802.11) (Engineering Samples) SMD module, ESP32-C3, 4MB SPI flash, PCB antenna, -40 C +105 C"
"U2","1","CP2102N-Axx-xQFN20","Package_DFN_QFN:SiliconLabs_QFN-20-1EP_3x3mm_P0.5mm_EP1.8x1.8mm","","USB to UART master bridge, QFN-20"
"U1","1","MCP73871-2CAI_ML","ESP32Footprints:QFN50P400X400X100-21N","Microchip Corp.","Microchip MCP73871-2CAI/ML, Battery Charge Controller, 1000mA, 20-Pin QFN | Microchip Technology Inc. MCP73871-2CAI/ML"
"TP5","1","TestCLK","TestPoint:TestPoint_Pad_1.0x1.0mm","","test point"
"TP4","1","TestCS","TestPoint:TestPoint_Pad_1.0x1.0mm","","test point"
"TP3","1","TestSD","TestPoint:TestPoint_Pad_1.0x1.0mm","","test point"
"TP2","1","TestMOSI","TestPoint:TestPoint_Pad_1.0x1.0mm","","test point"
"TP1","1","TestMISO","TestPoint:TestPoint_Pad_1.0x1.0mm","","test point"
"S2","1","ENABLE","TL3305AF260QG:SW_TL3305AF260QG","E-Switch","Tactile Switch SPST-NO Top Actuated Surface Mount"
"S1","1","BOOT","TL3305AF260QG:SW_TL3305AF260QG","E-Switch","Tactile Switch SPST-NO Top Actuated Surface Mount"
"R25,R26","2","2k","Resistor_SMD:R_0805_2012Metric","","Resistor"
"R23,R24","2","1M","Resistor_SMD:R_0805_2012Metric","","Resistor"
"R22","1","10k","Resistor_SMD:R_0805_2012Metric","","Resistor"
"R20,R21","2","4.7k","Resistor_SMD:R_0805_2012Metric","","Resistor"
"R19","1","100K","Resistor_SMD:R_0805_2012Metric","","Resistor"
"R15,R16,R17,R18","4","50","Resistor_SMD:R_0805_2012Metric","","Resistor"
"R14","1","47K5","Resistor_SMD:R_0805_2012Metric","","Resistor"
"R13","1","22K1","Resistor_SMD:R_0805_2012Metric","","Resistor"
"R7,R8,R9,R10,R11,R12","6","470","Resistor_SMD:R_0805_2012Metric","","Resistor"
"R6","1","20K","Resistor_SMD:R_0805_2012Metric","","Resistor"
"R5","1","2K","Resistor_SMD:R_0805_2012Metric","","Resistor"
"R3,R4","2","5K1","Resistor_SMD:R_0805_2012Metric","","Resistor"
"R2,R27,R28,R29,R30,R31","6","10K","Resistor_SMD:R_0805_2012Metric","","Resistor"
"R1","1","1k","Resistor_SMD:R_0805_2012Metric","","Resistor"
"Q2,Q3","2","BC817","Package_TO_SOT_SMD:SOT-23","","0.8A Ic, 45V Vce, NPN Transistor, SOT-23"
"Q1","1","TEMT6000X01","ESP32Footprints:TRANS_TEMT6000X01","VISHAY","Phototransistors 570nm Top View 1206 (3216 Metric)"
"MK1","1","CMC-5042PF-AC","ESP32Footprints:CUI_CMC-5042PF-AC","CUI INC","6.0 mm, Omnidirectional, PCB Mount, 2.0 Vdc, Electret Condenser Microphone"
"LED3","1","LTST-C170TBKT","ESP32Footprints:LEDC2012X120N","","LED,SMD,0805,Blue,28mcd,130deg"
"LED2,LED6","2","LTST-C170GKT","ESP32Footprints:LEDC2012X120N","","LED,SMD,0805,Green,6mcd,130deg Lite-On LTST-C170GKT, CHIPLED 0805 Series Green LED, 569 nm 2012 (0805), Rectangle Lens SMD package"
"LED1,LED4,LED5","3","LTST-C170KRKT","ESP32Footprints:LEDC2012X120N","","Standard LEDs - SMD Red Clear 631nm"
"J5","1","Conn_01x05_Pin","Connector_PinHeader_2.54mm:PinHeader_1x05_P2.54mm_Vertical","","Generic connector, single row, 01x05, script generated"
"J4","1","Conn_01x04_Pin","Connector_PinHeader_2.54mm:PinHeader_1x04_P2.54mm_Vertical","","Generic connector, single row, 01x04, script generated"
"J3","1","GSD090012SEU","ESP32Footprints:AMPHENOL_GSD090012SEU","Amphenol","Micro SD and SD Card Sockets, Input Output Connectors, SD Socket,9 Position,SMT"
"J2","1","B2B-PH-SM4-TB","ESP32Footprints:JST_B2B-PH-SM4-TB","JST","Connector Header Surface Mount 2 position 0.079 (2.00mm)"
"J1","1","SS-52400-002","ESP32Footprints:BELFUSE_SS-52400-002","BelFuse","USB Type-C Connector | USB 3.1 | 1 Port | Right Angle Receptacle | Shielded | 0.039 in (1.00mm) PCB Thickness"
"F1","1","0ZCH0110AF2E","ESP32Footprints:FUSC3226X100N","","1210 SMT PPTC | 1.10 Ih | 16V"
"C24,C25","2","10n","Capacitor_SMD:C_0805_2012Metric","","Unpolarized capacitor"
"C23","1","100n","Capacitor_SMD:C_0805_2012Metric","","Unpolarized capacitor"
"C19","1","0.01u","Capacitor_SMD:C_0805_2012Metric","","Unpolarized capacitor"
"C18","1","1u","Capacitor_SMD:C_0805_2012Metric","","Unpolarized capacitor"
"C17","1","100p","Capacitor_SMD:C_0805_2012Metric","","Unpolarized capacitor"
"C13","1","1Ou","ESP32Footprints:T491A","","Unpolarized capacitor"
"C12","1","0.1U","Capacitor_SMD:C_0805_2012Metric","","Unpolarized capacitor"
"C4,C6,C8,C9,C11,C14,C16,C20,C21,C22,C26","11","0.1u","Capacitor_SMD:C_0805_2012Metric","","Unpolarized capacitor"
"C2,C3,C10","3","4.7u","ESP32Footprints:T491A","","Unpolarized capacitor"
"C1,C5,C7,C15","4","10u","ESP32Footprints:T491A","","Unpolarized capacitor"
